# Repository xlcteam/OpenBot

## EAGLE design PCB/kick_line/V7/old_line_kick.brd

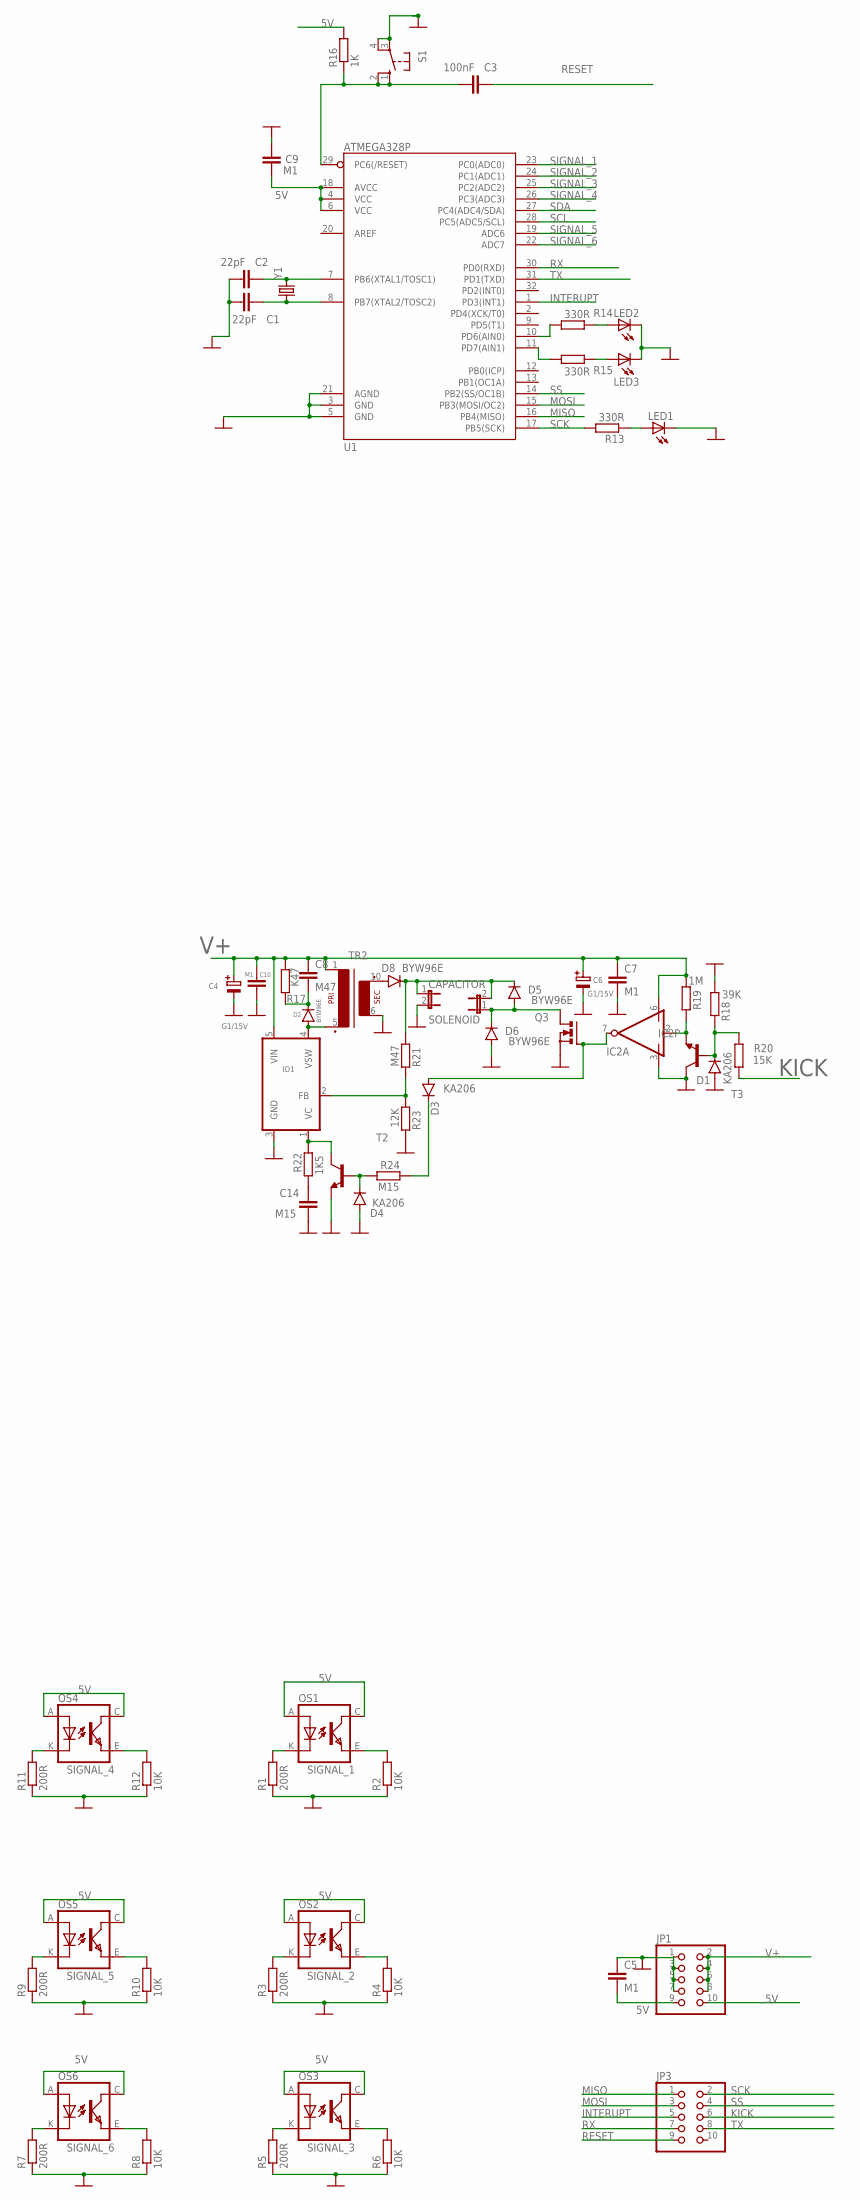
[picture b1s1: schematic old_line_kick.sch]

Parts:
C1, C2: 22pF; C0603
C3: 100nF; C0603
C4, C6: G1/15V; E-2,5/7-RAD
C5, C9: M1; C0603
C7, C10: M1; C0805K
C8: M47; C1206K
C14: M15; C0805K
CAPACITOR: JP1E; JP1
D1, D3, D4: KA206; D-7.5
D2, D5, D6, D8: BYW96E; SOD64-10
IC2: MIC4423BM; SO08
IO1: LT1071V; TO220-5P
JP1, JP3: PINHD-2X5IDC; 2X05_IDC
LED1, LED2, LED3: LEDCHIPLED_0603; CHIPLED_0603
OS1, OS2, OS3, OS4, OS5, OS6: TCRT5000
Q3: PMOSFET_NTO220BV; TO220BV
R1, R3, R5, R7, R9, R11: 200R; R0603
R2, R4, R6, R8, R10, R12: 10K; R0603
R13, R14, R15: 330R; R0603
R16: 1K; R0603
R17: K47; R0603
R18: 39K; R0603
R19: 1M; R0603
R20: 15K; R0603
R21: M47; R0603
R22: 1K5; R0603
R23: 12K; R0603
R24: M15; R0603
S1: 10-XX; B3F-10XX
SOLENOID: JP1E; JP1
T2, T3: -NPN-SC59-BEC; SC59-BEC
TR2: TRAFO-E10-R""; TRAFO-EE17X20
U1: ATMEGA328P; TQFP32-08
Y1: CRYSTALHC49US; HC49US

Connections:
5V: C5.2, C9.1, JP1.9, JP1.10, OS1.A (ANODE), OS1.C (COLLECTOR), OS2.A (ANODE), OS2.C (COLLECTOR), OS3.A (ANODE), OS3.C (COLLECTOR), OS4.A (ANODE), OS4.C (COLLECTOR), OS5.A (ANODE), OS5.C (COLLECTOR), OS6.A (ANODE), OS6.C (COLLECTOR), R16.2, U1.4 (VCC), U1.6 (VCC), U1.18 (AVCC)
GND: C1.1, C2.1, C4.-, C5.1, C6.-, C7.2, C9.2, C10.2, C14.2, CAPACITOR.2, D1.A, D4.A, D6.A, IC2.3 (GND), IO1.3 (GND), JP1.1, JP1.3, JP1.5, JP1.7, LED1.C, LED2.C, LED3.C, Q3.S, R1.1, R2.1, R3.1, R4.1, R5.1, R6.1, R7.1, R8.1, R9.1, R10.1, R11.1, R12.1, R18.2, R23.1, S1.3, S1.4 (P1), T2.E, T3.C, TR2.6 (3), U1.3 (GND), U1.5 (GND), U1.21 (AGND)
INTERUPT: JP3.5, U1.1 (PD3(INT1))
KICK: JP3.6, R20.1
MISO: JP3.1, U1.16 (PB4(MISO))
MOSI: JP3.3, U1.15 (PB3(MOSI/OC2))
unnamed: OS1.K (CATHODE), R1.2
unnamed: OS2.K (CATHODE), R3.2
unnamed: OS3.K (CATHODE), R5.2
unnamed: OS6.K (CATHODE), R7.2
unnamed: OS5.K (CATHODE), R9.2
unnamed: OS4.K (CATHODE), R11.2
unnamed: C2.2, U1.7 (PB6(XTAL1/TOSC1)), Y1.2
unnamed: C1.2, U1.8 (PB7(XTAL2/TOSC2)), Y1.1
unnamed: IO1.1 (VC), R22.1, T2.C
unnamed: C14.1, R22.2
unnamed: D8.A, TR2.10 (4)
unnamed: D3.A, IC2.7 (OUT), Q3.G
unnamed: CAPACITOR.1, D5.C, D8.C, R21.2, SOLENOID.2
unnamed: IO1.2 (FB), R21.1, R23.2
unnamed: D4.C, R24.2, T2.B
unnamed: C3.1, R16.1, S1.1 (S), S1.2 (S1), U1.29 (PC6(/RESET))
unnamed: LED1.A, R13.1
unnamed: IC2.2 (IN), R19.1, T3.E
unnamed: LED2.A, R14.1
unnamed: R15.2, U1.11 (PD7(AIN1))
unnamed: LED3.A, R15.1
unnamed: R14.2, U1.10 (PD6(AIN0))
unnamed: D2.A, IO1.4 (VSW), TR2.5 (2)
unnamed: C8.2, D2.C, R17.2
unnamed: D5.A, D6.C, Q3.D, SOLENOID.1
unnamed: D3.C, R24.1
unnamed: D1.C, R18.1, R20.2, T3.B
RESET: C3.2, JP3.9
RX: JP3.7, U1.30 (PD0(RXD))
SCK: JP3.2, R13.2, U1.17 (PB5(SCK))
SCL: U1.28 (PC5(ADC5/SCL))
SDA: U1.27 (PC4(ADC4/SDA))
SIGNAL_1: OS1.E (EMITTER), R2.2, U1.23 (PC0(ADC0))
SIGNAL_2: OS2.E (EMITTER), R4.2, U1.24 (PC1(ADC1))
SIGNAL_3: OS3.E (EMITTER), R6.2, U1.25 (PC2(ADC2))
SIGNAL_4: OS4.E (EMITTER), R12.2, U1.26 (PC3(ADC3))
SIGNAL_5: OS5.E (EMITTER), R10.2, U1.19 (ADC6)
SIGNAL_6: OS6.E (EMITTER), R8.2, U1.22 (ADC7)
SS: JP3.4, U1.14 (PB2(SS/OC1B))
TX: JP3.8, U1.31 (PD1(TXD))
V+: C4.+, C6.+, C7.1, C8.1, C10.1, IC2.6 (V+), IO1.5 (VIN), JP1.2, JP1.4, JP1.6, JP1.8, R17.1, R19.2, TR2.1

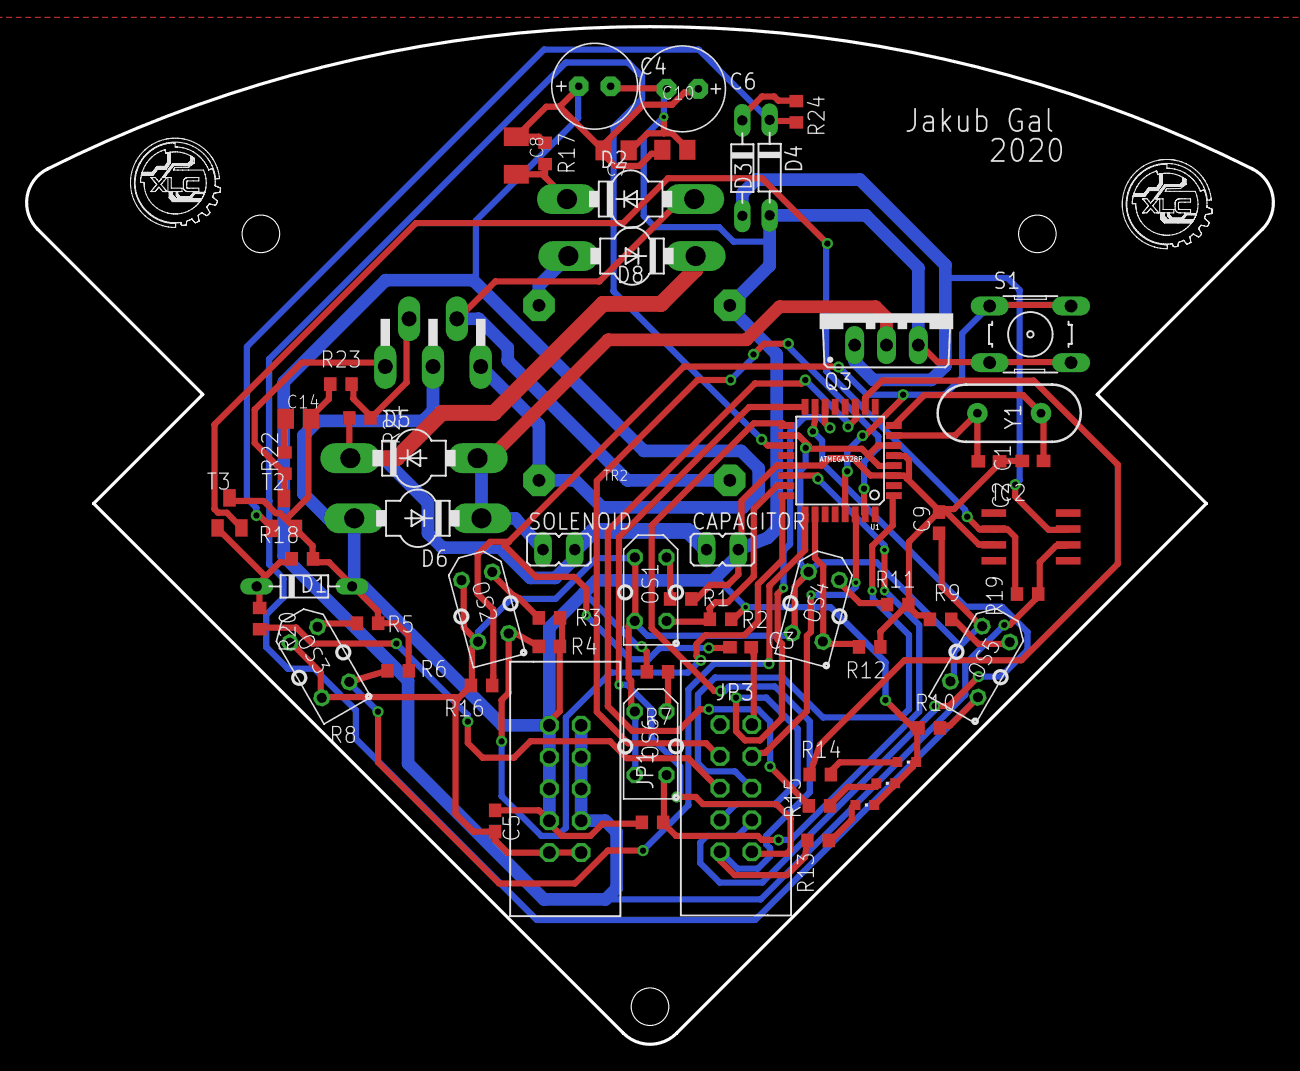
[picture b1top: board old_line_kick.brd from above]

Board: 2 copper layers, 99.5 x 81.3 mm, 64 parts (0 on the bottom side), 45 nets.

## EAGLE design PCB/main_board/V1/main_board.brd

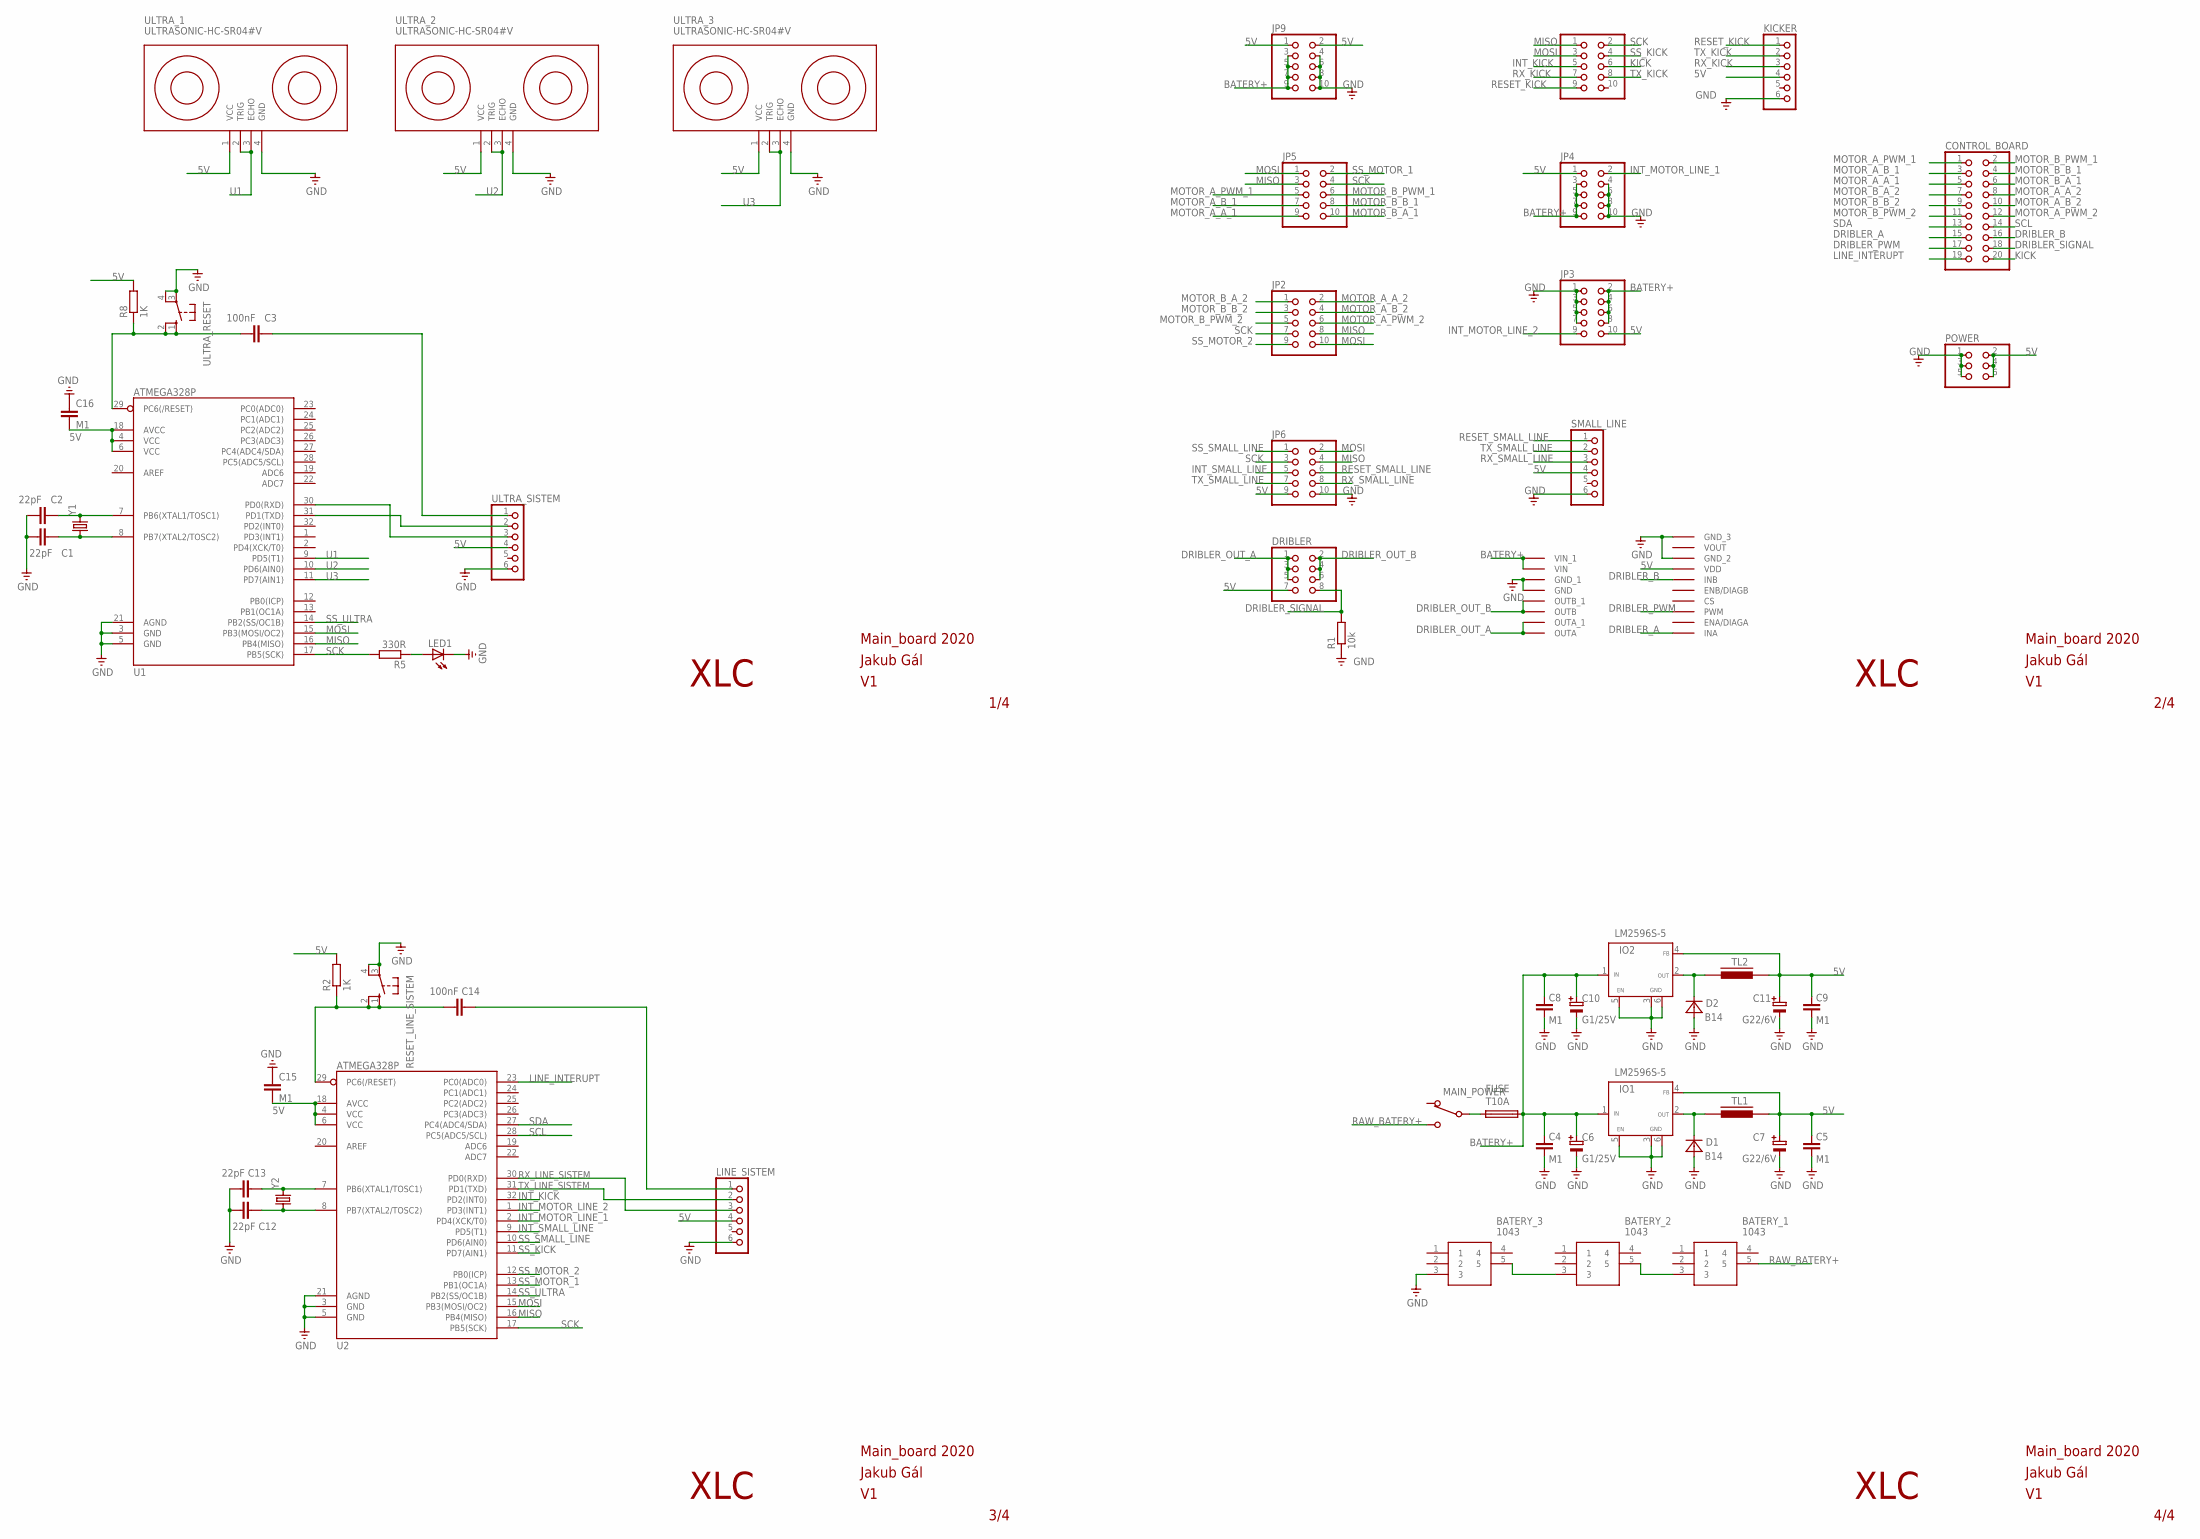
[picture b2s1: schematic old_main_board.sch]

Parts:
BATERY_1, BATERY_2, BATERY_3: 1043
C1, C2, C12, C13: 22pF; C0603
C3, C14: 100nF; C0603
C4, C5, C8, C9: M1; SMD-1206
C6, C10: G1/25V; SMD-ELE-D
C7, C11: G22/6V; SMD-ELE-D
C15, C16: M1; C0603
CONTROL_BOARD: PINHD-2X10_2.54-SMD; 2X10SMD
D1, D2: B14; D-3,6X5,5
DRIBLER: PINHD-2X4_2.54-SMD; 2X04SMD
FUSE: T10A; SH22,5A
IO1, IO2: LM2596S-5; TO263-5
JP2, JP3, JP4, JP5, JP6, JP8, JP9: PINHD-2X5_2.54-SMD; 2X05SMD
KICKER: PINHD-1X6; 1X06
LED1: LEDCHIPLED_0603; CHIPLED_0603
LINE_SISTEM: PINHD-1X6; 1X06
MAIN_POWER: PREP-1PB; P-B069B
POWER: PINHD-2X3_2.54-SMD; 2X03SMD
R1: 10k; R0603
R2, R8: 1K; R0603
R5: 330R; R0603
RESET_LINE_SISTEM: 10-XX; B3F-10XX
SMALL_LINE: PINHD-1X6; 1X06
TL1, TL2: INDUK-TLSMD1; INDUK-TL
U1, U2: ATMEGA328P; TQFP32-08
U$4: MOTOR_DRIVER
ULTRA_1, ULTRA_2, ULTRA_3: ULTRASONIC-HC-SR04#V
ULTRA_RESET: 10-XX; B3F-10XX
ULTRA_SISTEM: PINHD-1X6; 1X06
Y1, Y2: CRYSTALHC49US; HC49US

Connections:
5V: C5.2, C7.PLUS, C9.2, C11.PLUS, C15.2, C16.2, DRIBLER.7, IO1.4 (FB), IO2.4 (FB), JP3.10, JP4.1, JP6.9, JP9.1, JP9.2, KICKER.4, LINE_SISTEM.4, POWER.2, POWER.4, POWER.6, R2.2, R8.2, SMALL_LINE.4, TL1.2, TL2.2, U1.4 (VCC), U1.6 (VCC), U1.18 (AVCC), U2.4 (VCC), U2.6 (VCC), U2.18 (AVCC), U$4.VDD, ULTRA_1.1 (VCC), ULTRA_2.1 (VCC), ULTRA_3.1 (VCC), ULTRA_SISTEM.4
BATERY+: C4.2, C6.PLUS, C8.2, C10.PLUS, FUSE.2, IO1.1 (IN), IO2.1 (IN), JP3.2, JP3.4, JP3.6, JP3.8, JP4.3, JP4.5, JP4.7, JP4.9, JP9.3, JP9.5, JP9.7, JP9.9, U$4.VIN, U$4.VIN_1
DRIBLER_A: CONTROL_BOARD.15, U$4.INA
DRIBLER_B: CONTROL_BOARD.16, U$4.INB
DRIBLER_OUT_A: DRIBLER.1, DRIBLER.3, DRIBLER.5, U$4.OUTA, U$4.OUTA_1
DRIBLER_OUT_B: DRIBLER.2, DRIBLER.4, DRIBLER.6, U$4.OUTB, U$4.OUTB_1
DRIBLER_PWM: CONTROL_BOARD.17, U$4.PWM
DRIBLER_SIGNAL: CONTROL_BOARD.18, DRIBLER.8, R1.2
GND: BATERY_3.3, C1.1, C2.1, C4.1, C5.1, C6.MINUS, C7.MINUS, C8.1, C9.1, C10.MINUS, C11.MINUS, C12.1, C13.1, C15.1, C16.1, D1.A, D2.A, IO1.3 (GND), IO1.5 (EN), IO1.6 (GND), IO2.3 (GND), IO2.5 (EN), IO2.6 (GND), JP3.1, JP3.3, JP3.5, JP3.7, JP4.4, JP4.6, JP4.8, JP4.10, JP6.10, JP9.4, JP9.6, JP9.8, JP9.10, KICKER.6, LED1.C, LINE_SISTEM.6, POWER.1, POWER.3, POWER.5, R1.1, RESET_LINE_SISTEM.3, RESET_LINE_SISTEM.4 (P1), SMALL_LINE.6, U1.3 (GND), U1.5 (GND), U1.21 (AGND), U2.3 (GND), U2.5 (GND), U2.21 (AGND), U$4.GND, U$4.GND_1, U$4.GND_2, U$4.GND_3, ULTRA_1.4 (GND), ULTRA_2.4 (GND), ULTRA_3.4 (GND), ULTRA_RESET.3, ULTRA_RESET.4 (P1), ULTRA_SISTEM.6
INT_KICK: JP8.5, U2.32 (PD2(INT0))
INT_MOTOR_LINE_1: JP4.2, U2.2 (PD4(XCK/T0))
INT_MOTOR_LINE_2: JP3.9, U2.1 (PD3(INT1))
INT_SMALL_LINE: JP6.5, U2.9 (PD5(T1))
KICK: CONTROL_BOARD.20, JP8.6
LINE_INTERUPT: CONTROL_BOARD.19, U2.23 (PC0(ADC0))
MISO: JP2.8, JP5.3, JP6.4, JP8.1, U1.16 (PB4(MISO)), U2.16 (PB4(MISO))
MOSI: JP2.10, JP5.1, JP6.2, JP8.3, U1.15 (PB3(MOSI/OC2)), U2.15 (PB3(MOSI/OC2))
MOTOR_A_A_1: CONTROL_BOARD.5, JP5.9
MOTOR_A_A_2: CONTROL_BOARD.8, JP2.2
MOTOR_A_B_1: CONTROL_BOARD.3, JP5.7
MOTOR_A_B_2: CONTROL_BOARD.10, JP2.4
MOTOR_A_PWM_1: CONTROL_BOARD.1, JP5.5
MOTOR_A_PWM_2: CONTROL_BOARD.12, JP2.6
MOTOR_B_A_1: CONTROL_BOARD.6, JP5.10
MOTOR_B_A_2: CONTROL_BOARD.7, JP2.1
MOTOR_B_B_1: CONTROL_BOARD.4, JP5.8
MOTOR_B_B_2: CONTROL_BOARD.9, JP2.3
MOTOR_B_PWM_1: CONTROL_BOARD.2, JP5.6
MOTOR_B_PWM_2: CONTROL_BOARD.11, JP2.5
unnamed: BATERY_1.3, BATERY_2.5
unnamed: BATERY_2.3, BATERY_3.5
unnamed: D2.K, IO2.2 (OUT), TL2.1
unnamed: FUSE.1, MAIN_POWER.2 (2-COM)
unnamed: C13.2, U2.7 (PB6(XTAL1/TOSC1)), Y2.2
unnamed: D1.K, IO1.2 (OUT), TL1.1
unnamed: C2.2, U1.7 (PB6(XTAL1/TOSC1)), Y1.2
unnamed: C1.2, U1.8 (PB7(XTAL2/TOSC2)), Y1.1
unnamed: C12.2, U2.8 (PB7(XTAL2/TOSC2)), Y2.1
unnamed: C14.2, LINE_SISTEM.1
unnamed: C14.1, R2.1, RESET_LINE_SISTEM.1 (S), RESET_LINE_SISTEM.2 (S1), U2.29 (PC6(/RESET))
unnamed: U1.30 (PD0(RXD)), ULTRA_SISTEM.3
unnamed: U1.31 (PD1(TXD)), ULTRA_SISTEM.2
unnamed: C3.2, ULTRA_SISTEM.1
unnamed: C3.1, R8.1, U1.29 (PC6(/RESET)), ULTRA_RESET.1 (S), ULTRA_RESET.2 (S1)
unnamed: LED1.A, R5.1
RAW_BATERY+: BATERY_1.5, MAIN_POWER.1 (1-OFF)
RESET_KICK: JP8.9, KICKER.1
RESET_SMALL_LINE: JP6.6, SMALL_LINE.1
RX_KICK: JP8.7, KICKER.3
RX_LINE_SISTEM: LINE_SISTEM.3, U2.30 (PD0(RXD))
RX_SMALL_LINE: JP6.8, SMALL_LINE.3
SCK: JP2.7, JP5.4, JP6.3, JP8.2, R5.2, U1.17 (PB5(SCK)), U2.17 (PB5(SCK))
SCL: CONTROL_BOARD.14, U2.28 (PC5(ADC5/SCL))
SDA: CONTROL_BOARD.13, U2.27 (PC4(ADC4/SDA))
SS_KICK: JP8.4, U2.11 (PD7(AIN1))
SS_MOTOR_1: JP5.2, U2.13 (PB1(OC1A))
SS_MOTOR_2: JP2.9, U2.12 (PB0(ICP))
SS_SMALL_LINE: JP6.1, U2.10 (PD6(AIN0))
SS_ULTRA: U1.14 (PB2(SS/OC1B)), U2.14 (PB2(SS/OC1B))
TX_KICK: JP8.8, KICKER.2
TX_LINE_SISTEM: LINE_SISTEM.2, U2.31 (PD1(TXD))
TX_SMALL_LINE: JP6.7, SMALL_LINE.2
U1: U1.9 (PD5(T1)), ULTRA_1.2 (TRIG), ULTRA_1.3 (ECHO)
U2: U1.10 (PD6(AIN0)), ULTRA_2.2 (TRIG), ULTRA_2.3 (ECHO)
U3: U1.11 (PD7(AIN1)), ULTRA_3.2 (TRIG), ULTRA_3.3 (ECHO)

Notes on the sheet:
1/4
2/4
3/4
4/4
XLC
Main_board 2020
Jakub Gál

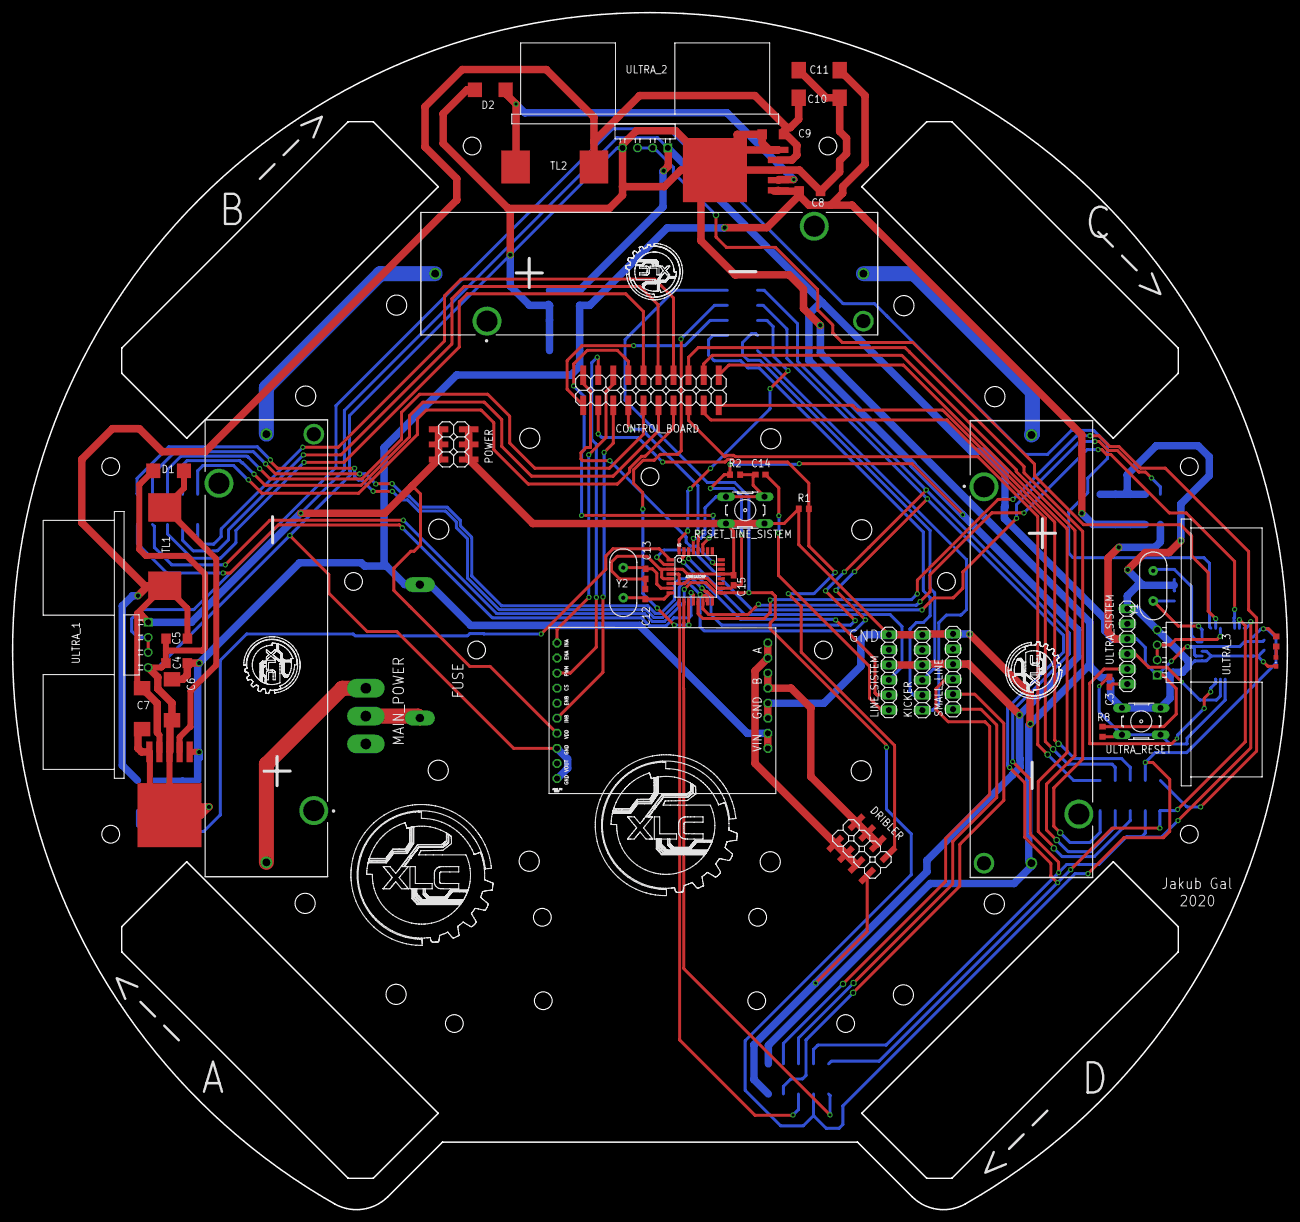
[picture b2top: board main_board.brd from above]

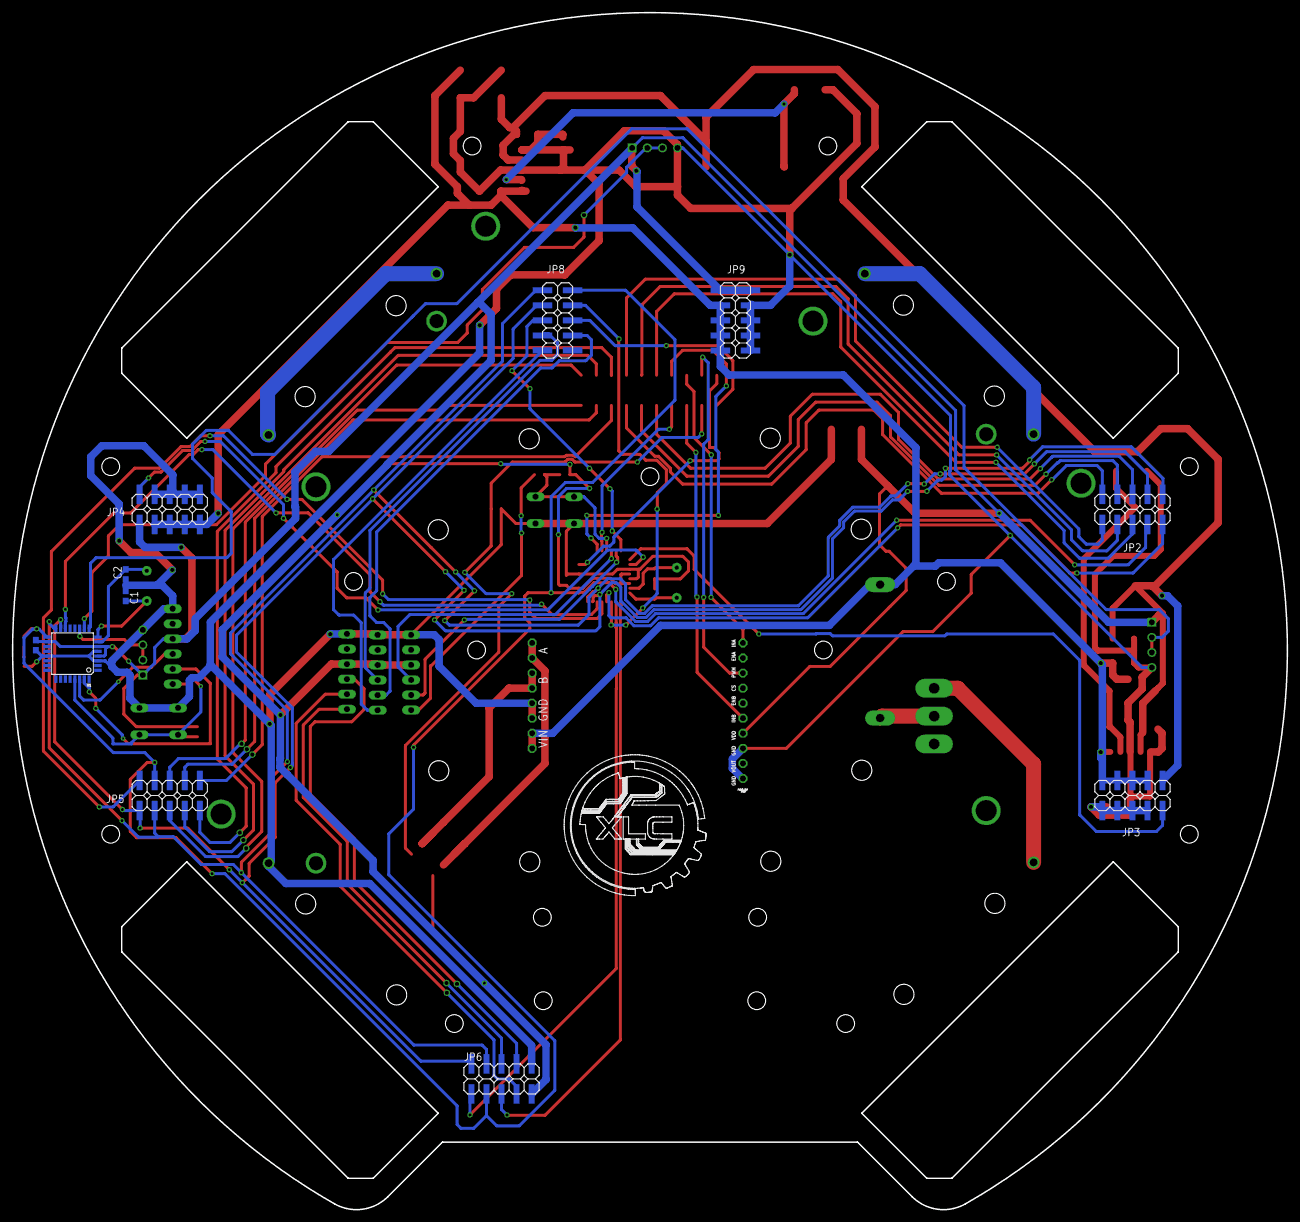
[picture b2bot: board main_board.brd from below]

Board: 2 copper layers, 215.0 x 201.9 mm, 56 parts (11 on the bottom side), 65 nets.

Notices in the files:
parts and their libraries:
SparkFun-DigitalIC: Licensing: CC v3.0 Share-Alike You are welcome to use this library for commercial purposes.
diy-modules: Released under the Creative Commons Attribution 4.0 International License: http://creativecommons.org/licenses/by/4.0
